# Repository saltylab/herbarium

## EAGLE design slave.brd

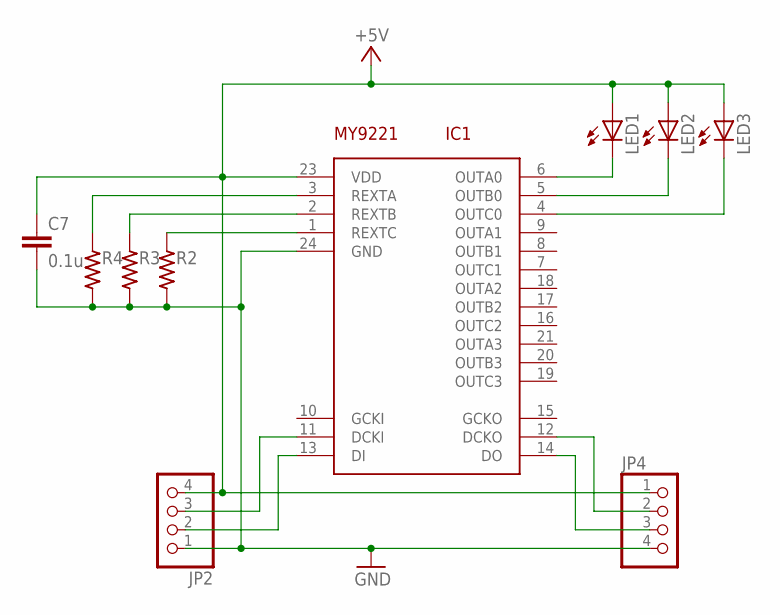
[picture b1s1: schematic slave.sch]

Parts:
C7: 0.1u; C1608
IC1: MY9221SS; SSOP24
JP2, JP4: PINHD-1X4; 1X04
LED1, LED2, LED3: LED5MM
R2, R3, R4: RESISTOR-US1608; SMD1608

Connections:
+5V: C7.1, IC1.23 (VDD), JP2.4, JP4.1, LED1.A, LED2.A, LED3.A
GND: C7.2, IC1.24 (GND), JP2.1, JP4.4, R2.2, R3.2, R4.2
unnamed: IC1.11 (DCKI), JP2.3
unnamed: IC1.13 (DI), JP2.2
unnamed: IC1.12 (DCKO), JP4.2
unnamed: IC1.14 (DO), JP4.3
unnamed: IC1.1 (REXTC), R2.1
unnamed: IC1.2 (REXTB), R3.1
unnamed: IC1.3 (REXTA), R4.1
unnamed: IC1.6 (OUTA0), LED1.K (C)
unnamed: IC1.5 (OUTB0), LED2.K (C)
unnamed: IC1.4 (OUTC0), LED3.K (C)

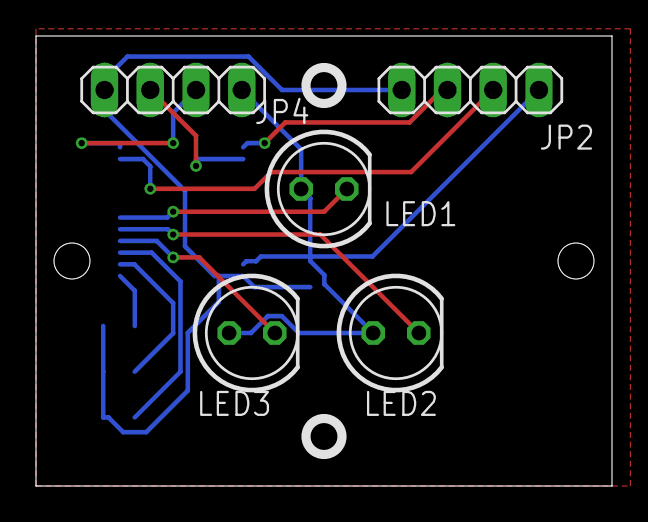
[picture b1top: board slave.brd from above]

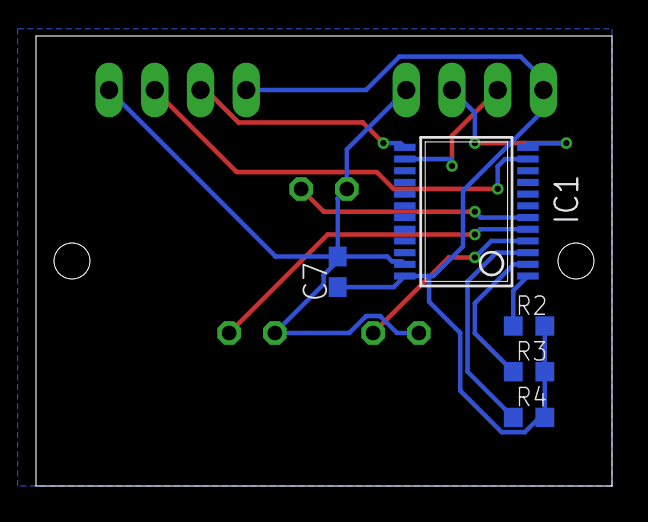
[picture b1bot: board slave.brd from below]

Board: 2 copper layers, 32.0 x 25.0 mm, 10 parts (5 on the bottom side), 12 nets.

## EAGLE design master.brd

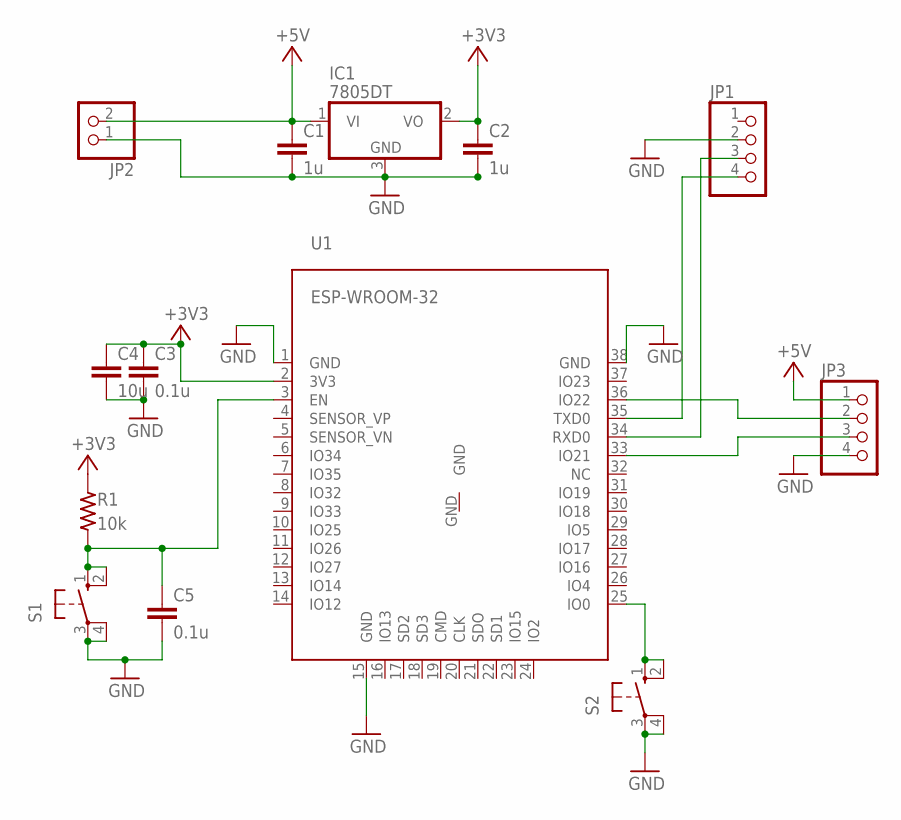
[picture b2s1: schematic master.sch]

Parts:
C1, C2: 1u; C1608
C3, C5: 0.1u; C1608
C4: 10u; C1608
IC1: 7805DT; TO252
JP1, JP3: PINHD-1X4; 1X04
JP2: PINHD-1X2; 1X02
R1: 10k; SMD1608
S1, S2: 10-XX; B3F-10XX
U1: ESP-WROOM-32

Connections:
+3V3: C2.1, C3.1, C4.1, IC1.2 (VO), R1.1, U1.2 (3V3)
+5V: C1.1, IC1.1 (VI), JP2.2, JP3.1
GND: C1.2, C2.2, C3.2, C4.2, C5.2, IC1.3 (GND), JP1.2, JP2.1, JP3.4, S1.3, S1.4 (P1), S2.3, S2.4 (P1), U1.1 (GND), U1.15 (GND), U1.38 (GND)
unnamed: JP1.3, U1.34 (RXD0)
unnamed: JP1.4, U1.35 (TXD0)
unnamed: S2.1 (S), S2.2 (S1), U1.25 (IO0)
unnamed: C5.1, R1.2, S1.1 (S), S1.2 (S1), U1.3 (EN)
unnamed: JP3.2, U1.36 (IO22)
unnamed: JP3.3, U1.33 (IO21)

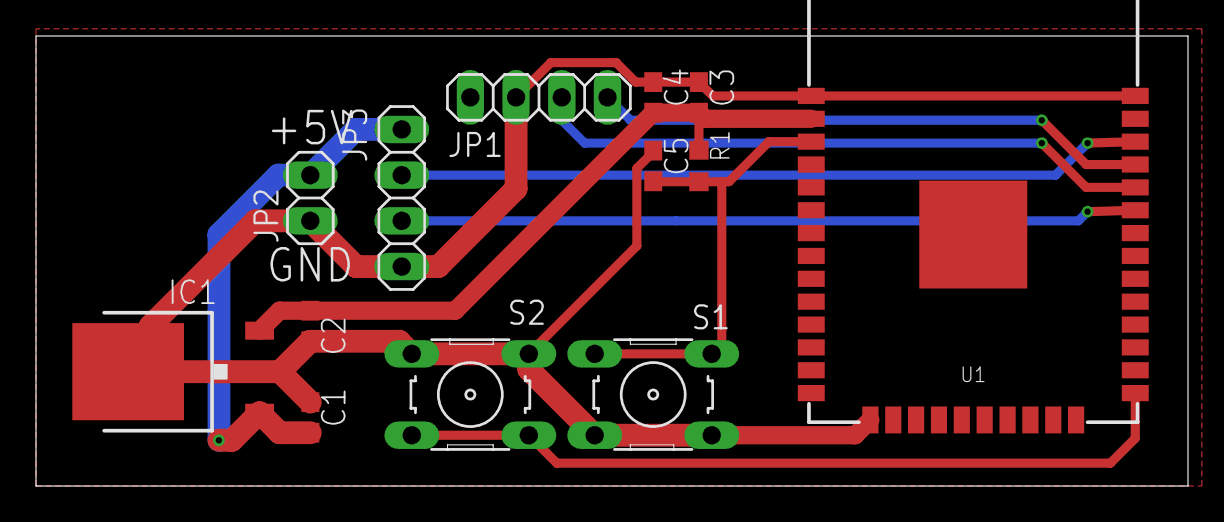
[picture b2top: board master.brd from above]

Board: 2 copper layers, 64.0 x 25.0 mm, 13 parts (0 on the bottom side), 9 nets.

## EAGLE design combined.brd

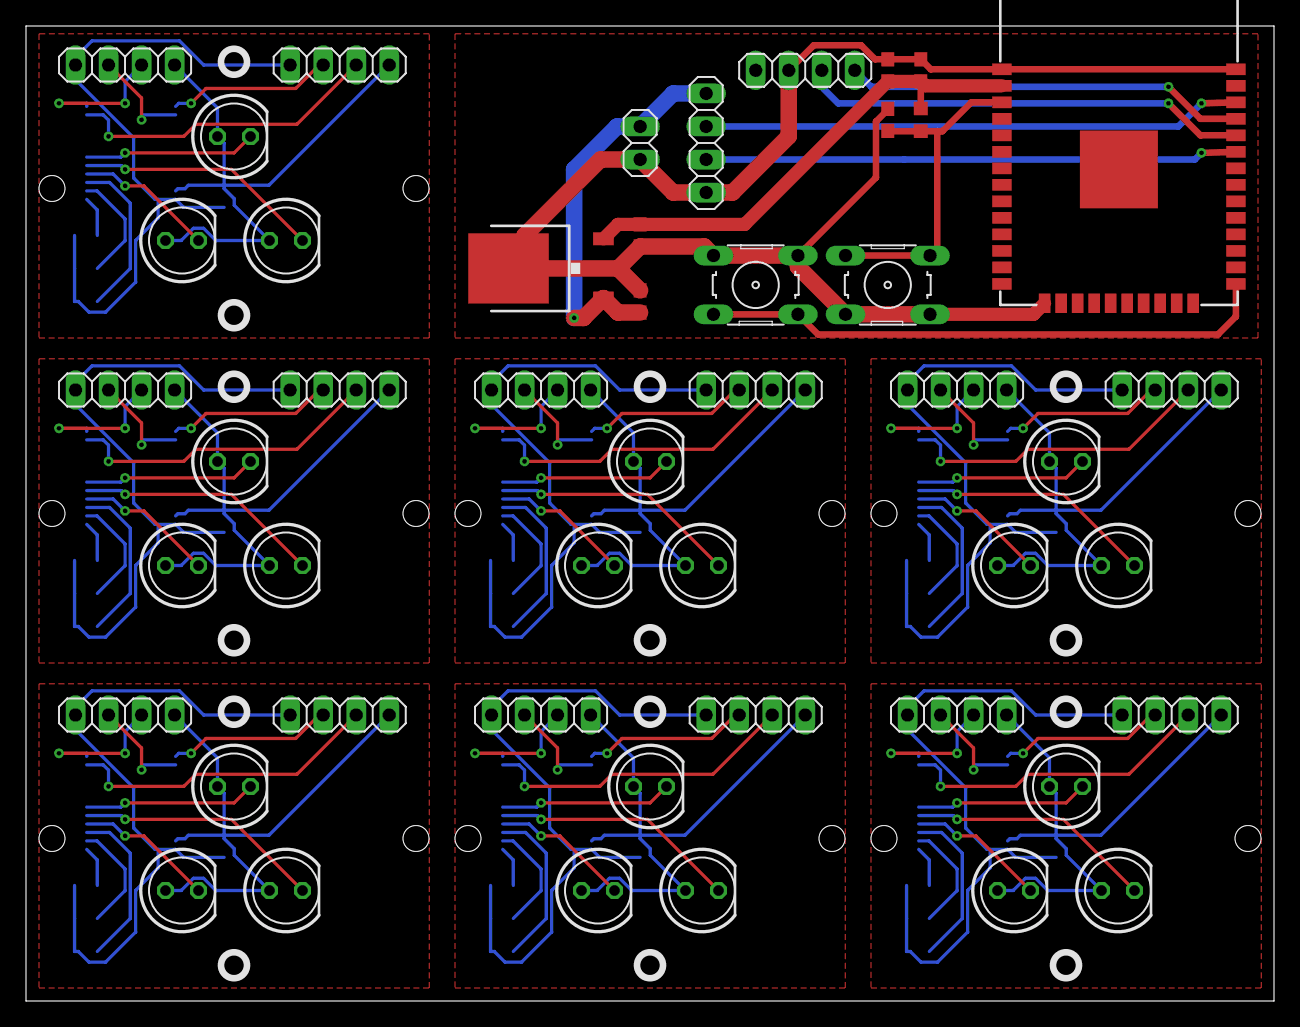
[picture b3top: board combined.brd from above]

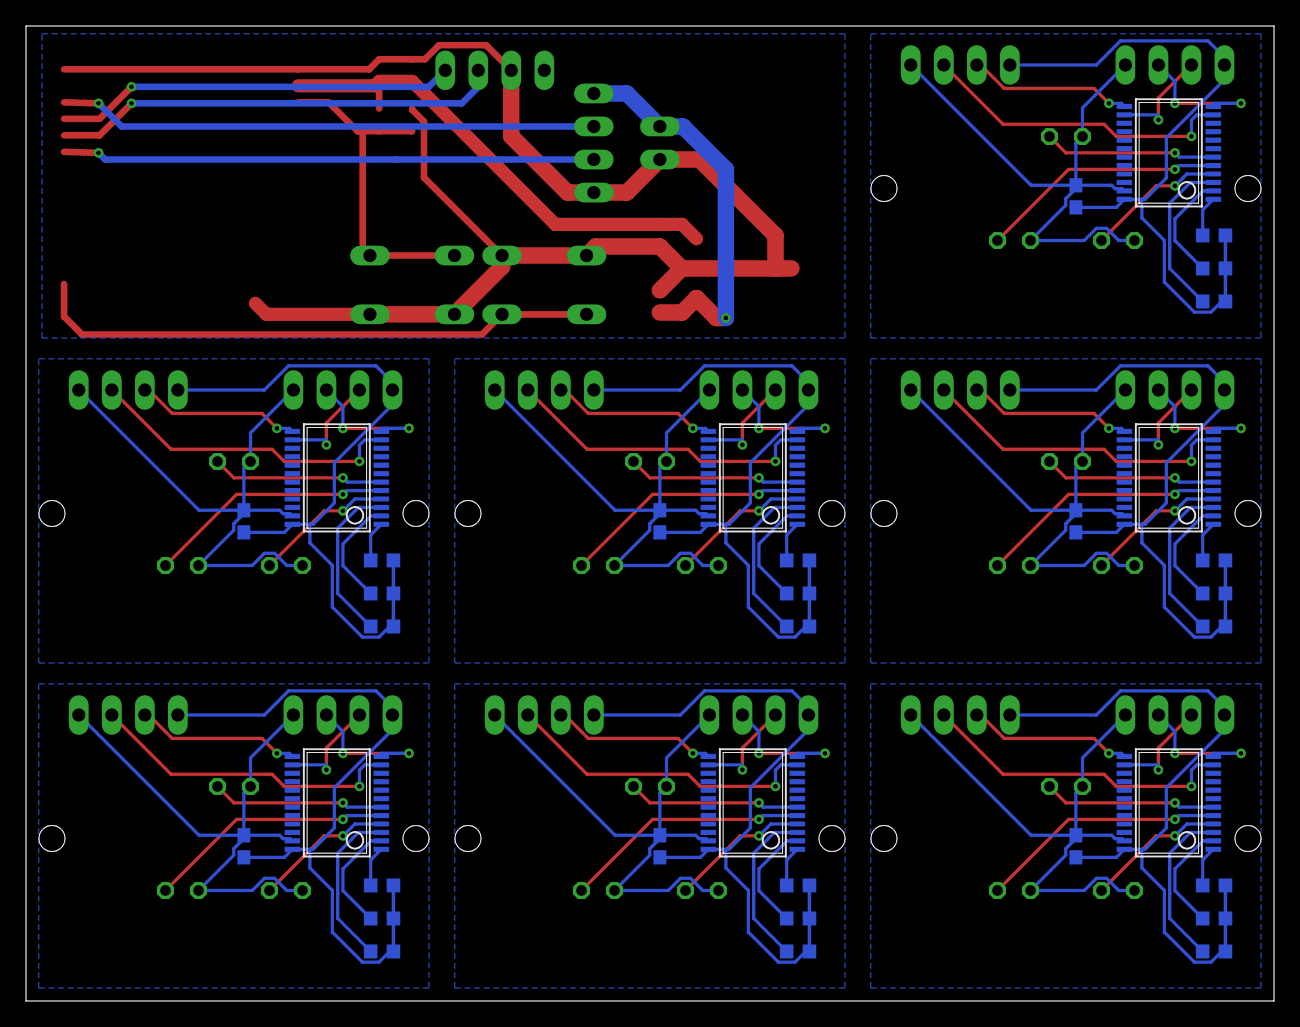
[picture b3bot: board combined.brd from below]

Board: 2 copper layers, 96.0 x 75.0 mm, 83 parts (35 on the bottom side), 93 nets.

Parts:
C1, C2, C3, C4, C5, C6, C7, C10, C12: 0.1u; C1608
C8, C9: 1u; C1608
C11: 10u; C1608
IC1, IC2, IC3, IC4, IC5, IC6, IC7: MY9221SS; SSOP24
IC8: 7805DT; TO252
JP1, JP2, JP3, JP4, JP5, JP6, JP7, JP8, JP9, JP10, JP11, JP12, JP13, JP14, JP15, JP16: 1X04
JP17: 1X02
LED1, LED2, LED3, LED4, LED5, LED6, LED7, LED8, LED9, LED10, LED11, LED12, LED13, LED14, LED15, LED16, LED17, LED18, LED19, LED20, LED21: LED5MM
R1, R2, R3, R4, R5, R6, R7, R8, R9, R10, R11, R12, R13, R14, R15, R16, R17, R18, R19, R20, R21: SMD1608
R22: 10k; SMD1608
S1, S2: B3F-10XX
U1: ESP-WROOM-32

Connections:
+3V3: C9.1, C10.1, C11.1, IC8.2, R22.1, U1.2
+5V: C7.1, IC1.23, JP2.4, JP4.1, LED1.A, LED2.A, LED3.A
+5V1: C1.1, IC2.23, JP1.4, JP3.1, LED4.A, LED5.A, LED6.A
+5V2: C2.1, IC3.23, JP5.4, JP6.1, LED7.A, LED8.A, LED9.A
+5V3: C3.1, IC4.23, JP7.4, JP8.1, LED10.A, LED11.A, LED12.A
+5V4: C4.1, IC5.23, JP9.4, JP10.1, LED13.A, LED14.A, LED15.A
+5V5: C5.1, IC6.23, JP11.4, JP12.1, LED16.A, LED17.A, LED18.A
+5V6: C6.1, IC7.23, JP13.4, JP14.1, LED19.A, LED20.A, LED21.A
+5V7: C8.1, IC8.1, JP16.1, JP17.2
GND: C7.2, IC1.24, JP2.1, JP4.4, R2.2, R3.2, R4.2
GND1: C1.2, IC2.24, JP1.1, JP3.4, R1.2, R5.2, R6.2
GND2: C2.2, IC3.24, JP5.1, JP6.4, R7.2, R8.2, R9.2
GND3: C3.2, IC4.24, JP7.1, JP8.4, R10.2, R11.2, R12.2
GND4: C4.2, IC5.24, JP9.1, JP10.4, R13.2, R14.2, R15.2
GND5: C5.2, IC6.24, JP11.1, JP12.4, R16.2, R17.2, R18.2
GND6: C6.2, IC7.24, JP13.1, JP14.4, R19.2, R20.2, R21.2
GND7: C8.2, C9.2, C10.2, C11.2, C12.2, IC8.3, JP15.2, JP16.4, JP17.1, S1.3, S1.4, S2.3, S2.4, U1.1, U1.15, U1.38
unnamed: IC1.11, JP2.3
unnamed: IC2.11, JP1.3
unnamed: IC2.13, JP1.2
unnamed: IC1.13, JP2.2
unnamed: IC2.12, JP3.2
unnamed: IC2.14, JP3.3
unnamed: IC1.12, JP4.2
unnamed: IC2.1, R1.1
unnamed: IC1.14, JP4.3
unnamed: IC2.2, R5.1
unnamed: IC2.3, R6.1
unnamed: IC2.6, LED4.K
unnamed: IC2.5, LED5.K
unnamed: IC1.1, R2.1
unnamed: IC1.2, R3.1
unnamed: IC1.3, R4.1
unnamed: IC1.6, LED1.K
unnamed: IC1.5, LED2.K
unnamed: IC1.4, LED3.K
unnamed: IC2.4, LED6.K
unnamed: IC3.11, JP5.3
unnamed: IC3.13, JP5.2
unnamed: IC3.12, JP6.2
unnamed: IC3.14, JP6.3
unnamed: IC3.1, R7.1
unnamed: IC3.2, R8.1
unnamed: IC3.3, R9.1
unnamed: IC3.6, LED7.K
unnamed: IC3.5, LED8.K
unnamed: IC3.4, LED9.K
unnamed: IC4.11, JP7.3
unnamed: IC4.13, JP7.2
unnamed: IC4.12, JP8.2
unnamed: IC4.14, JP8.3
unnamed: IC4.1, R10.1
unnamed: IC4.2, R11.1
unnamed: IC4.3, R12.1
unnamed: IC4.6, LED10.K
unnamed: IC4.5, LED11.K
unnamed: IC4.4, LED12.K
unnamed: IC5.11, JP9.3
unnamed: IC5.13, JP9.2
unnamed: IC5.12, JP10.2
unnamed: IC5.14, JP10.3
unnamed: IC5.1, R13.1
unnamed: IC5.2, R14.1
unnamed: IC5.3, R15.1
unnamed: IC5.6, LED13.K
unnamed: IC5.5, LED14.K
unnamed: IC5.4, LED15.K
unnamed: IC6.11, JP11.3
unnamed: IC6.13, JP11.2
unnamed: IC6.12, JP12.2
unnamed: IC6.14, JP12.3
unnamed: IC6.1, R16.1
unnamed: IC6.2, R17.1
unnamed: IC6.3, R18.1
unnamed: IC6.6, LED16.K
unnamed: IC6.5, LED17.K
unnamed: IC6.4, LED18.K
unnamed: IC7.11, JP13.3
unnamed: IC7.13, JP13.2
unnamed: IC7.12, JP14.2
unnamed: IC7.14, JP14.3
unnamed: IC7.1, R19.1
unnamed: IC7.2, R20.1
unnamed: IC7.3, R21.1
unnamed: IC7.6, LED19.K
unnamed: IC7.5, LED20.K
unnamed: IC7.4, LED21.K
unnamed: JP15.3, U1.34
unnamed: JP15.4, U1.35
unnamed: S2.1, S2.2, U1.25
unnamed: C12.1, R22.2, S1.1, S1.2, U1.3
unnamed: JP16.2, U1.36
unnamed: JP16.3, U1.33
